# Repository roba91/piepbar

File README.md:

piepbar
=======

Fachschaftsgetränke 2.0

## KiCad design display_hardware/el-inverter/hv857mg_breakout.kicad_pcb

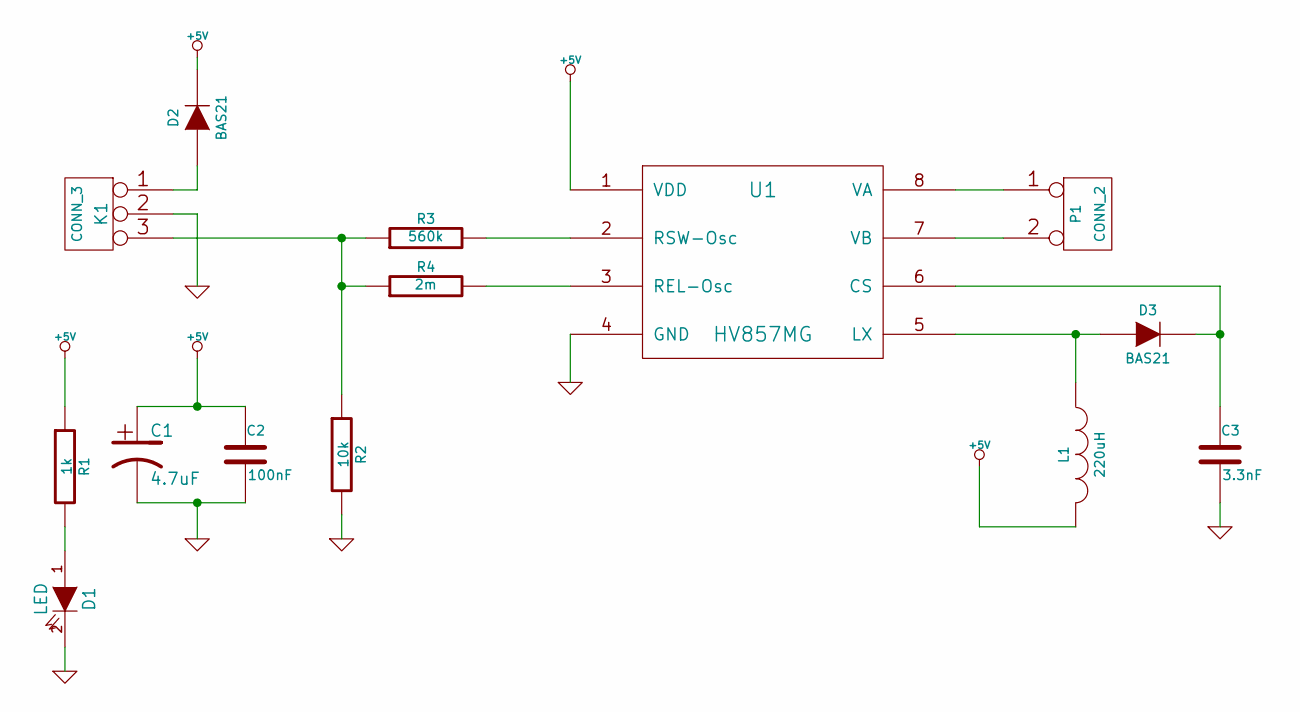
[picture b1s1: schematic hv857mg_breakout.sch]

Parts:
C1: 4.7uF
C2: 100nF
C3: 3.3nF
D1: LED
D2, D3: BAS21
K1: CONN_3
L1: 220uH
P1: CONN_2
R1: 1k
R2: 10k
R3: 560k
R4: 2m
U1: HV857MG

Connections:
+5V: C1.1, C2.1, D2.2 (K), L1.2, R1.1, U1.1 (VDD)
GND: C1.2, C2.2, C3.2, D1.2 (K), K1.2 (PM), R2.2, U1.4 (GND)
unnamed: K1.3, R2.1, R3.1, R4.1
unnamed: D2.1 (A), K1.1
unnamed: D1.1 (A), R1.2
unnamed: R4.2, U1.3 (REL-Osc)
unnamed: C3.1, D3.2 (K), U1.6 (CS)
unnamed: R3.2, U1.2 (RSW-Osc)
unnamed: P1.2 (PM), U1.7 (VB)
unnamed: P1.1, U1.8 (VA)
unnamed: D3.1 (A), L1.1, U1.5 (LX)

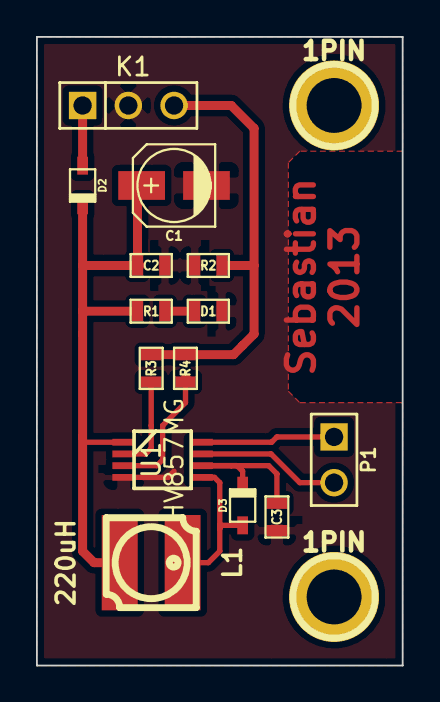
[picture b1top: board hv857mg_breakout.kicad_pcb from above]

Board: 2 copper layers, 20.3 x 34.9 mm, 16 parts (0 on the bottom side), 11 nets.

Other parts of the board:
1PIN, 1PIN#2: P***; 1pin

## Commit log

2013-06-09 initial files, no content
2013-06-09 Added display driver code
2013-06-10 Python code to communicate with the display added
2013-06-10 First 400 byte transfer works
2013-06-10 Sending 800byte blocks works
2013-06-12 __main__ gerüst
2013-06-12 basic purchase workflow implemented, communication stub
2013-06-12 PIL testing
2013-06-12 Fixed PIL import
2013-06-12 fixed global var issue
2013-06-12 refactoring -> now we can use the __init__.py file properly
2013-06-13 Added display font
2013-06-13 Added pil to display format conversion
2013-06-13 Move displaydriver into display module
2013-06-13 Display methods
2013-06-13 Fixed display.py Added displaydriver to init
2013-06-13 Fixed all some errors
2013-06-13 Fixed all/some errors
2013-06-13 Commucation with display works fine at 76800Baud
2013-06-13 Added some bitmaps for testing Removed unused fonts for microcontroller Cleaned some things up a bit
2013-06-13 refactored hanles; proper locking (not purchase and updates concurrently); nice code layout :)
2013-06-13 deleted old script (missed during refactoring)
2013-06-13 and again, missed this one, too
2013-06-14 locks are awesome now, timeout implemented
2013-06-14 nice http lib
2013-06-15 reworked display
2013-06-16 Improved message display
2013-06-16 Display message: Added multiline and center alignment
2013-06-16 remote stuff
2013-06-16 removed lock in favour of a working version with an event
2013-06-16 removed unused stuff
2013-06-17 display integration
2013-06-17 more granular message control; all messages are implemented
2013-06-18 implemented display for purchase; timeout messages still missing
2013-06-18 Major bugfix: corrected typo
2013-06-18 should be fair now
2013-06-18 fixed bug
2013-06-18 added piep to bar
2013-06-19 adjusted urls
2013-06-19 using put instead of post
2013-06-19 resolved issues; errors in the intranet backend are handled properly now
2013-06-19 Added trimming for long drinks and names
2013-06-19 removed debugs; proper remote handling
2013-06-19 added rake file for testing
2013-06-19 Lol python
2013-06-19 added debug msg and added an undo function to delete last selected item
2013-06-19 added missing import
2013-06-20 remote: try sync to avoid 422
2013-06-20 add requirement.txt for easier pip install
2013-06-20 missing s
2013-06-20 drings with umlaut work properly now
2013-06-20 config stuff
2013-06-20 deleted moved files
2013-07-13 Added schematic for display backlight driver
2013-07-14 Added footprint lib from http://smisioto.no-ip.org/ Started work on pcb
2013-07-14 Added udev rule for display hardware
2013-07-14 Finished pcb Cleanup work
2013-08-26 Moar stuff for the inverter
2013-08-26 Added better logging
2013-08-26 Fixed wrong logger
2013-08-29 Fixed broken logging in actions:reset Added logging for starting/stopping the system
2013-09-24 Fixed kab0rken logger statements
2014-04-03 Color display part 1
2014-07-10 Switched from PIL to Pillow Removed version numbers from requirements because they fucked pyserial up
2014-07-29 Anpassungen für Farbdisplay
2014-07-29 Cleared up some test data
2014-07-31 Added movie playback
2014-07-31 Improves random video selection
2014-08-01 Moar pictures
2014-08-20 Fix: set bills to zero if no user is scanned
2014-08-20 Fixed previous commit not fixing anything
2015-09-07 pep8 conform formatting
2015-09-07 System crashed when entering a non existing user.
    E.g. 'user__a' if there is no user with login name 'a'
2015-09-07 Canceling action when scaned username is not known by the intranet
2015-09-07 Quit sessions of blocked users
2015-09-08 Rolling back pep8 conform formatting. This code is ugly styled. Sorry
2016-01-13 Using new json api of the intranet.
